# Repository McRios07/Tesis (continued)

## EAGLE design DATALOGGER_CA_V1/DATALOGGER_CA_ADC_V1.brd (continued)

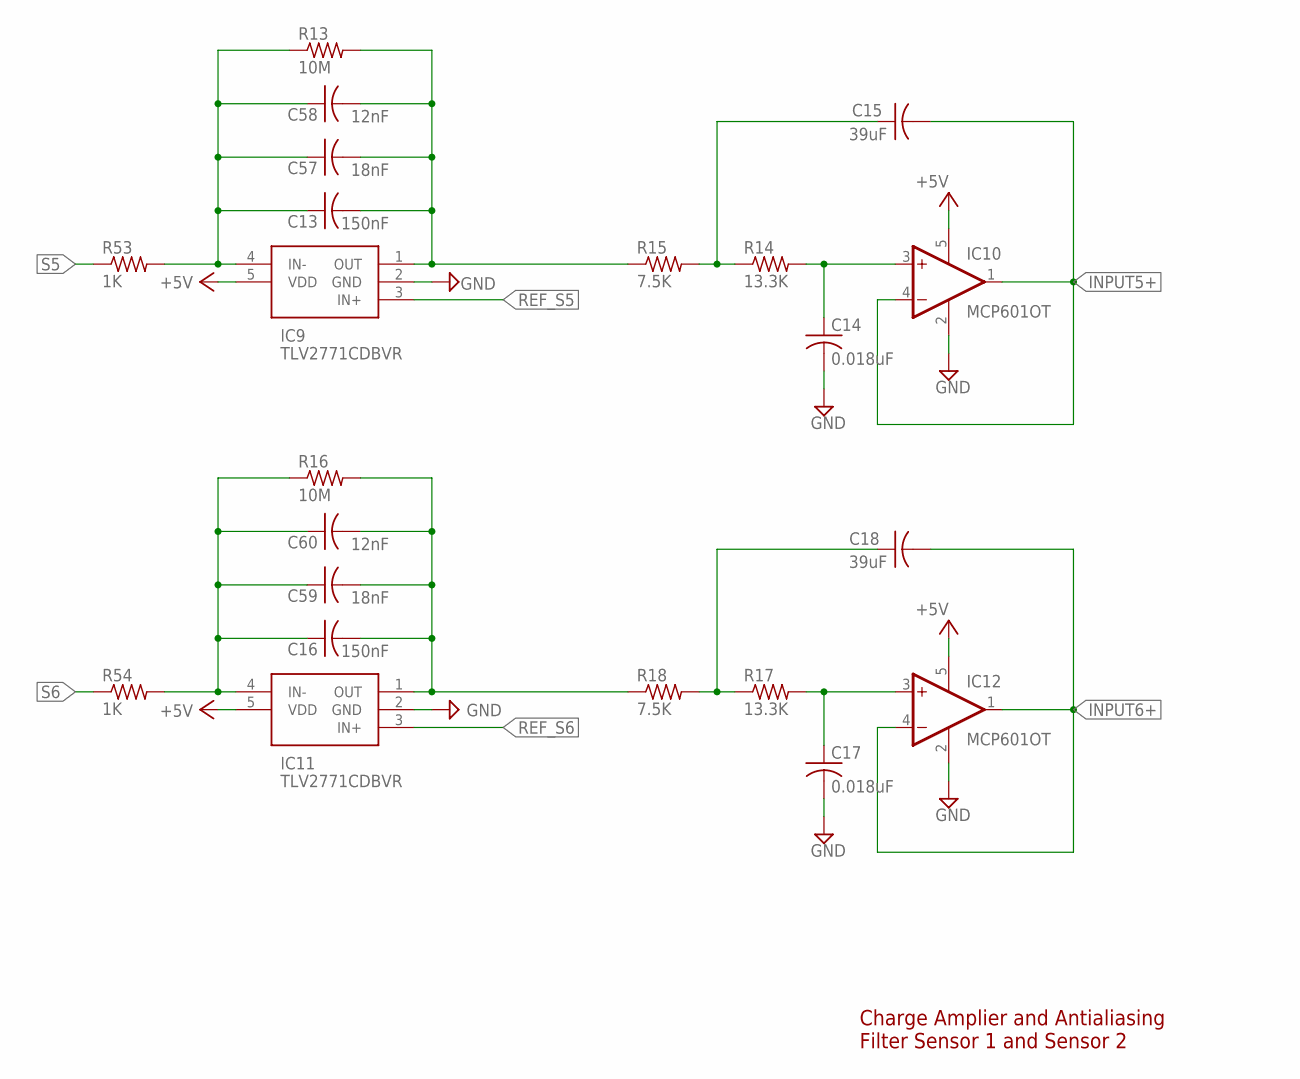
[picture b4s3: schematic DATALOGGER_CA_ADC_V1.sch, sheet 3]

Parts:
C13, C16: 150nF; C0805
C14, C17: 0.018uF; C0805
C15, C18: 39uF; C0805
C57, C59: 18nF; C0805
C58, C60: 12nF; C0805
IC9, IC11: TLV2771CDBVR; SOT95P280X145-5N
IC10, IC12: MCP601OT; SOT23-5
R13, R16: 10M; R0805
R14, R17: 13.3K; R0805
R15, R18: 7.5K; R0805
R53, R54: 1K; R0805

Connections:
+5V: IC9.5 (VDD), IC10.5 (V+), IC11.5 (VDD), IC12.5 (V+); also elsewhere on the board
GND: C14.2, C17.2, IC9.2 (GND), IC10.2 (V-), IC11.2 (GND), IC12.2 (V-); also elsewhere on the board
INPUT5+: C15.2, IC10.1 (OUT), IC10.4 (-IN); also elsewhere on the board
INPUT6+: C18.2, IC12.1 (OUT), IC12.4 (-IN); also elsewhere on the board
unnamed: C13.2, C57.2, C58.2, IC9.1 (OUT), R13.2, R15.1
unnamed: C14.1, IC10.3 (+IN), R14.2
unnamed: C15.1, R14.1, R15.2
unnamed: C16.2, C59.2, C60.2, IC11.1 (OUT), R16.2, R18.1
unnamed: C17.1, IC12.3 (+IN), R17.2
unnamed: C18.1, R17.1, R18.2
unnamed: C13.1, C57.1, C58.1, IC9.4 (IN-), R13.1, R53.2
unnamed: C16.1, C59.1, C60.1, IC11.4 (IN-), R16.1, R54.2
REF_S5: IC9.3 (IN+); also elsewhere on the board
REF_S6: IC11.3 (IN+); also elsewhere on the board
S5: R53.1; also elsewhere on the board
S6: R54.1; also elsewhere on the board

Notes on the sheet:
Charge Amplier and Antialiasing Filter Sensor 1 and Sensor 2

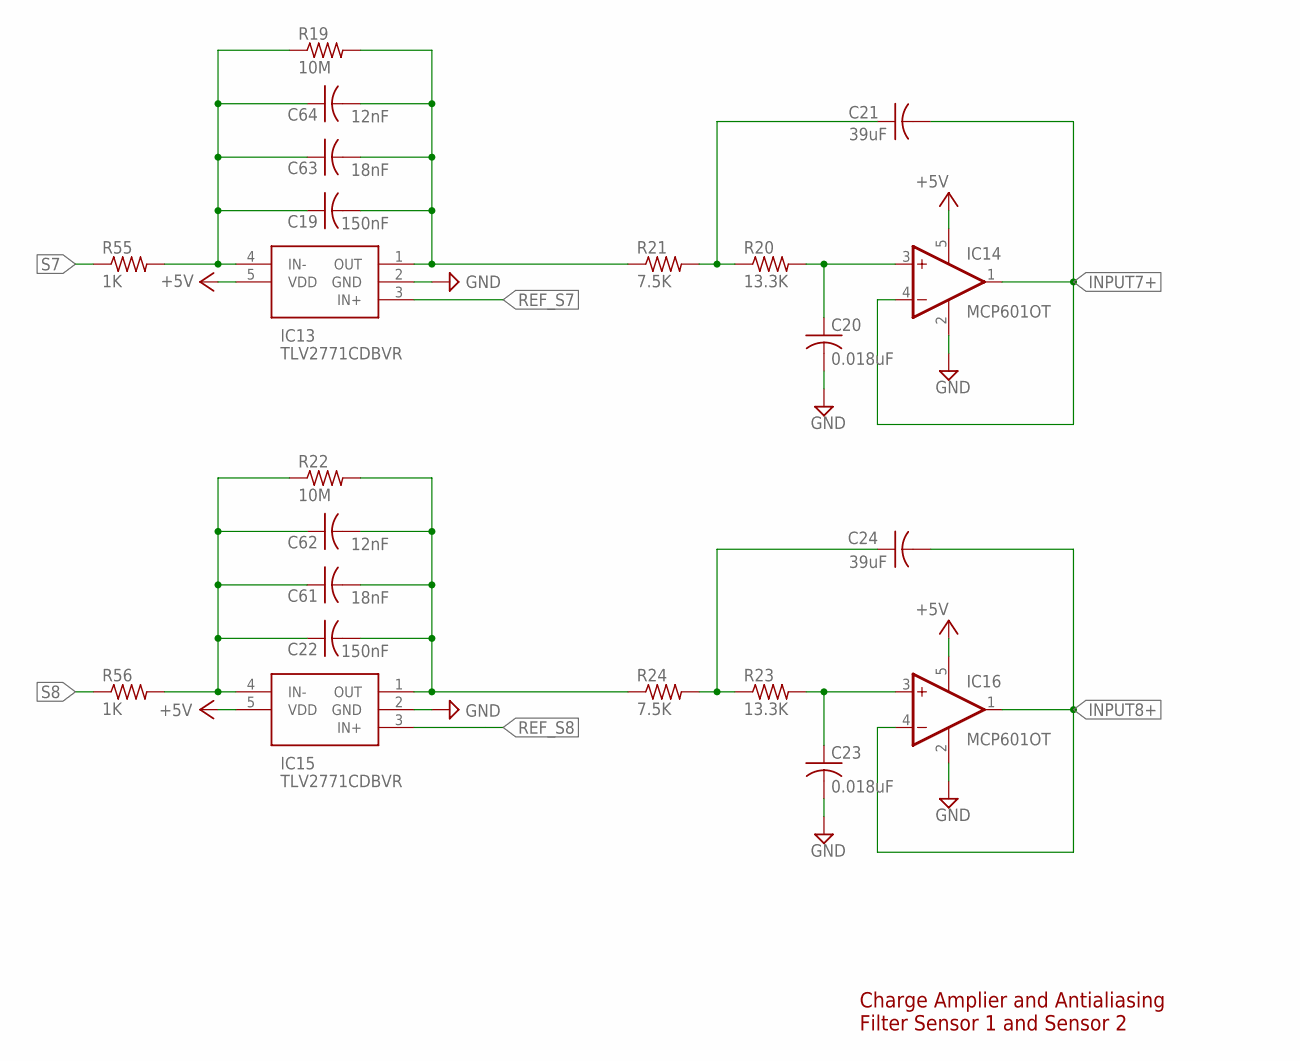
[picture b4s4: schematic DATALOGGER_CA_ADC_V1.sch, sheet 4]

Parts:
C19, C22: 150nF; C0805
C20, C23: 0.018uF; C0805
C21, C24: 39uF; C0805
C61, C63: 18nF; C0805
C62, C64: 12nF; C0805
IC13, IC15: TLV2771CDBVR; SOT95P280X145-5N
IC14, IC16: MCP601OT; SOT23-5
R19, R22: 10M; R0805
R20, R23: 13.3K; R0805
R21, R24: 7.5K; R0805
R55, R56: 1K; R0805

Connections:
+5V: IC13.5 (VDD), IC14.5 (V+), IC15.5 (VDD), IC16.5 (V+); also elsewhere on the board
GND: C20.2, C23.2, IC13.2 (GND), IC14.2 (V-), IC15.2 (GND), IC16.2 (V-); also elsewhere on the board
INPUT7+: C21.2, IC14.1 (OUT), IC14.4 (-IN); also elsewhere on the board
INPUT8+: C24.2, IC16.1 (OUT), IC16.4 (-IN); also elsewhere on the board
unnamed: C19.2, C63.2, C64.2, IC13.1 (OUT), R19.2, R21.1
unnamed: C20.1, IC14.3 (+IN), R20.2
unnamed: C21.1, R20.1, R21.2
unnamed: C22.2, C61.2, C62.2, IC15.1 (OUT), R22.2, R24.1
unnamed: C23.1, IC16.3 (+IN), R23.2
unnamed: C24.1, R23.1, R24.2
unnamed: C19.1, C63.1, C64.1, IC13.4 (IN-), R19.1, R55.2
unnamed: C22.1, C61.1, C62.1, IC15.4 (IN-), R22.1, R56.2
REF_S7: IC13.3 (IN+); also elsewhere on the board
REF_S8: IC15.3 (IN+); also elsewhere on the board
S7: R55.1; also elsewhere on the board
S8: R56.1; also elsewhere on the board

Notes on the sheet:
Charge Amplier and Antialiasing Filter Sensor 1 and Sensor 2

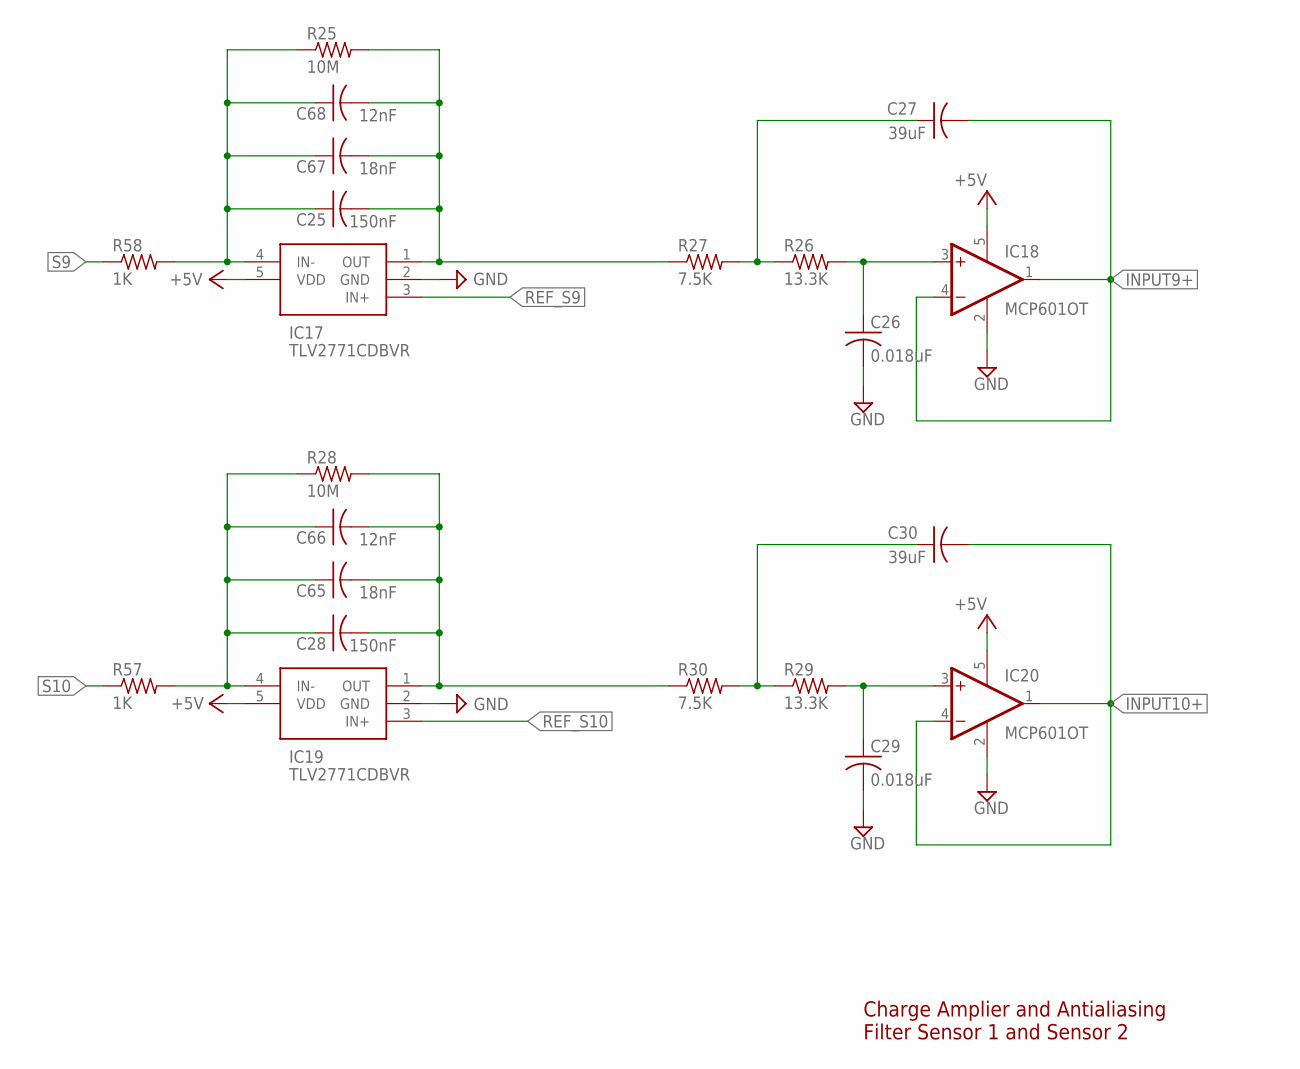
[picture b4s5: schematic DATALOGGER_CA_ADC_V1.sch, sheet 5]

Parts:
C25, C28: 150nF; C0805
C26, C29: 0.018uF; C0805
C27, C30: 39uF; C0805
C65, C67: 18nF; C0805
C66, C68: 12nF; C0805
IC17, IC19: TLV2771CDBVR; SOT95P280X145-5N
IC18, IC20: MCP601OT; SOT23-5
R25, R28: 10M; R0805
R26, R29: 13.3K; R0805
R27, R30: 7.5K; R0805
R57, R58: 1K; R0805

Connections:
+5V: IC17.5 (VDD), IC18.5 (V+), IC19.5 (VDD), IC20.5 (V+); also elsewhere on the board
GND: C26.2, C29.2, IC17.2 (GND), IC18.2 (V-), IC19.2 (GND), IC20.2 (V-); also elsewhere on the board
INPUT9+: C27.2, IC18.1 (OUT), IC18.4 (-IN); also elsewhere on the board
INPUT10+: C30.2, IC20.1 (OUT), IC20.4 (-IN); also elsewhere on the board
unnamed: C25.2, C67.2, C68.2, IC17.1 (OUT), R25.2, R27.1
unnamed: C26.1, IC18.3 (+IN), R26.2
unnamed: C27.1, R26.1, R27.2
unnamed: C28.2, C65.2, C66.2, IC19.1 (OUT), R28.2, R30.1
unnamed: C29.1, IC20.3 (+IN), R29.2
unnamed: C30.1, R29.1, R30.2
unnamed: C25.1, C67.1, C68.1, IC17.4 (IN-), R25.1, R58.2
unnamed: C28.1, C65.1, C66.1, IC19.4 (IN-), R28.1, R57.2
REF_S9: IC17.3 (IN+); also elsewhere on the board
REF_S10: IC19.3 (IN+); also elsewhere on the board
S9: R58.1; also elsewhere on the board
S10: R57.1; also elsewhere on the board

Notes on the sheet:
Charge Amplier and Antialiasing Filter Sensor 1 and Sensor 2

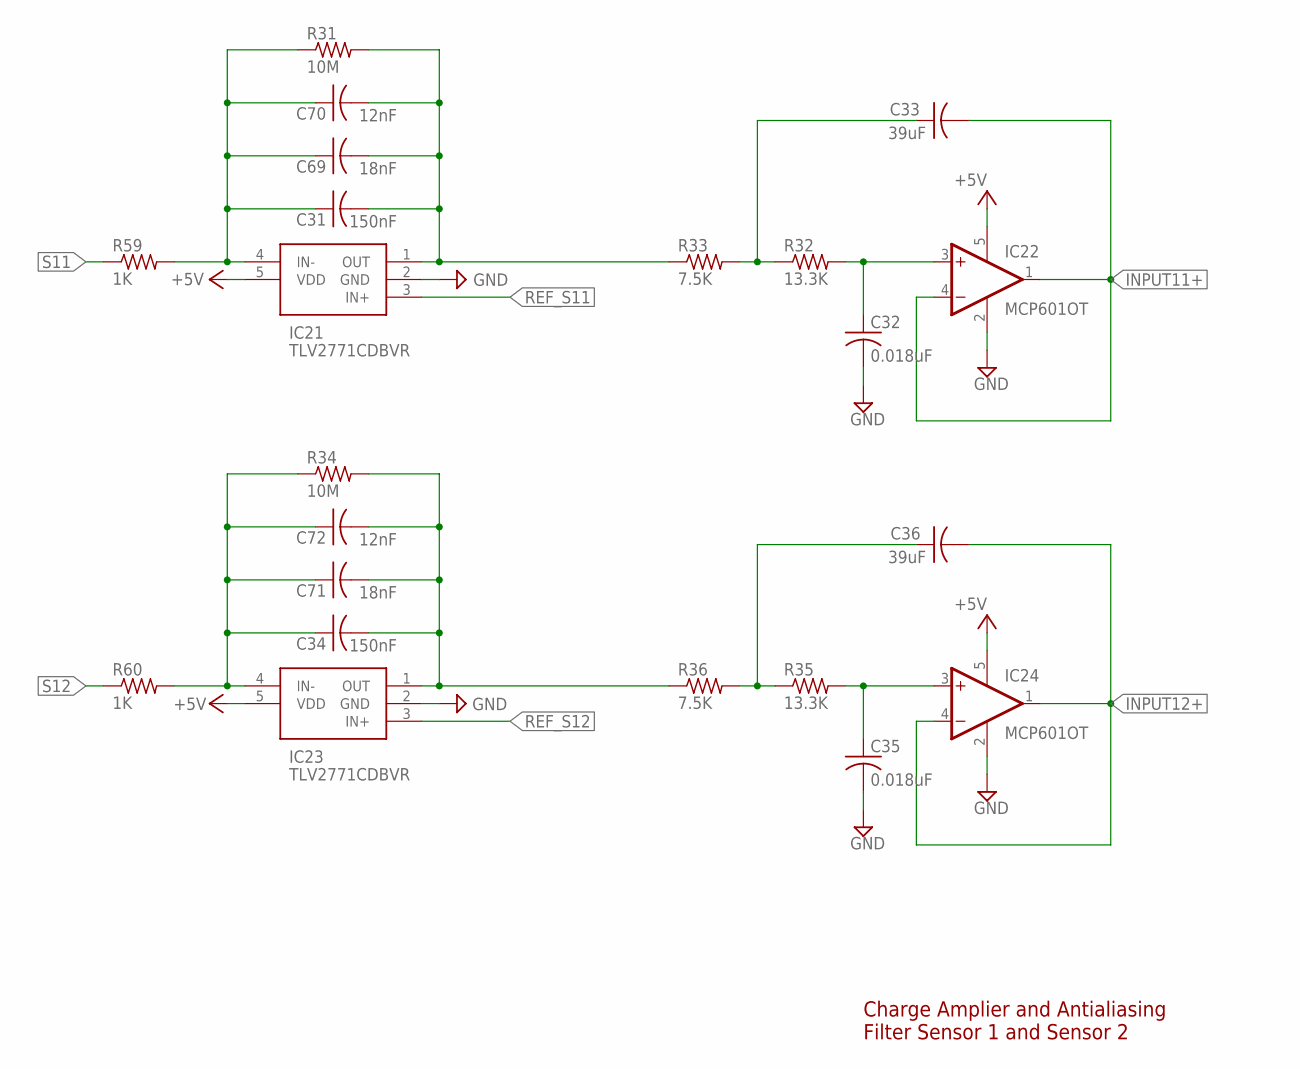
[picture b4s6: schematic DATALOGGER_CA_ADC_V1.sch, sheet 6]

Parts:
C31, C34: 150nF; C0805
C32, C35: 0.018uF; C0805
C33, C36: 39uF; C0805
C69, C71: 18nF; C0805
C70, C72: 12nF; C0805
IC21, IC23: TLV2771CDBVR; SOT95P280X145-5N
IC22, IC24: MCP601OT; SOT23-5
R31, R34: 10M; R0805
R32, R35: 13.3K; R0805
R33, R36: 7.5K; R0805
R59, R60: 1K; R0805

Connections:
+5V: IC21.5 (VDD), IC22.5 (V+), IC23.5 (VDD), IC24.5 (V+); also elsewhere on the board
GND: C32.2, C35.2, IC21.2 (GND), IC22.2 (V-), IC23.2 (GND), IC24.2 (V-); also elsewhere on the board
INPUT11+: C33.2, IC22.1 (OUT), IC22.4 (-IN); also elsewhere on the board
INPUT12+: C36.2, IC24.1 (OUT), IC24.4 (-IN); also elsewhere on the board
unnamed: C31.2, C69.2, C70.2, IC21.1 (OUT), R31.2, R33.1
unnamed: C32.1, IC22.3 (+IN), R32.2
unnamed: C33.1, R32.1, R33.2
unnamed: C34.2, C71.2, C72.2, IC23.1 (OUT), R34.2, R36.1
unnamed: C35.1, IC24.3 (+IN), R35.2
unnamed: C36.1, R35.1, R36.2
unnamed: C31.1, C69.1, C70.1, IC21.4 (IN-), R31.1, R59.2
unnamed: C34.1, C71.1, C72.1, IC23.4 (IN-), R34.1, R60.2
REF_S11: IC21.3 (IN+); also elsewhere on the board
REF_S12: IC23.3 (IN+); also elsewhere on the board
S11: R59.1; also elsewhere on the board
S12: R60.1; also elsewhere on the board

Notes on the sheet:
Charge Amplier and Antialiasing Filter Sensor 1 and Sensor 2

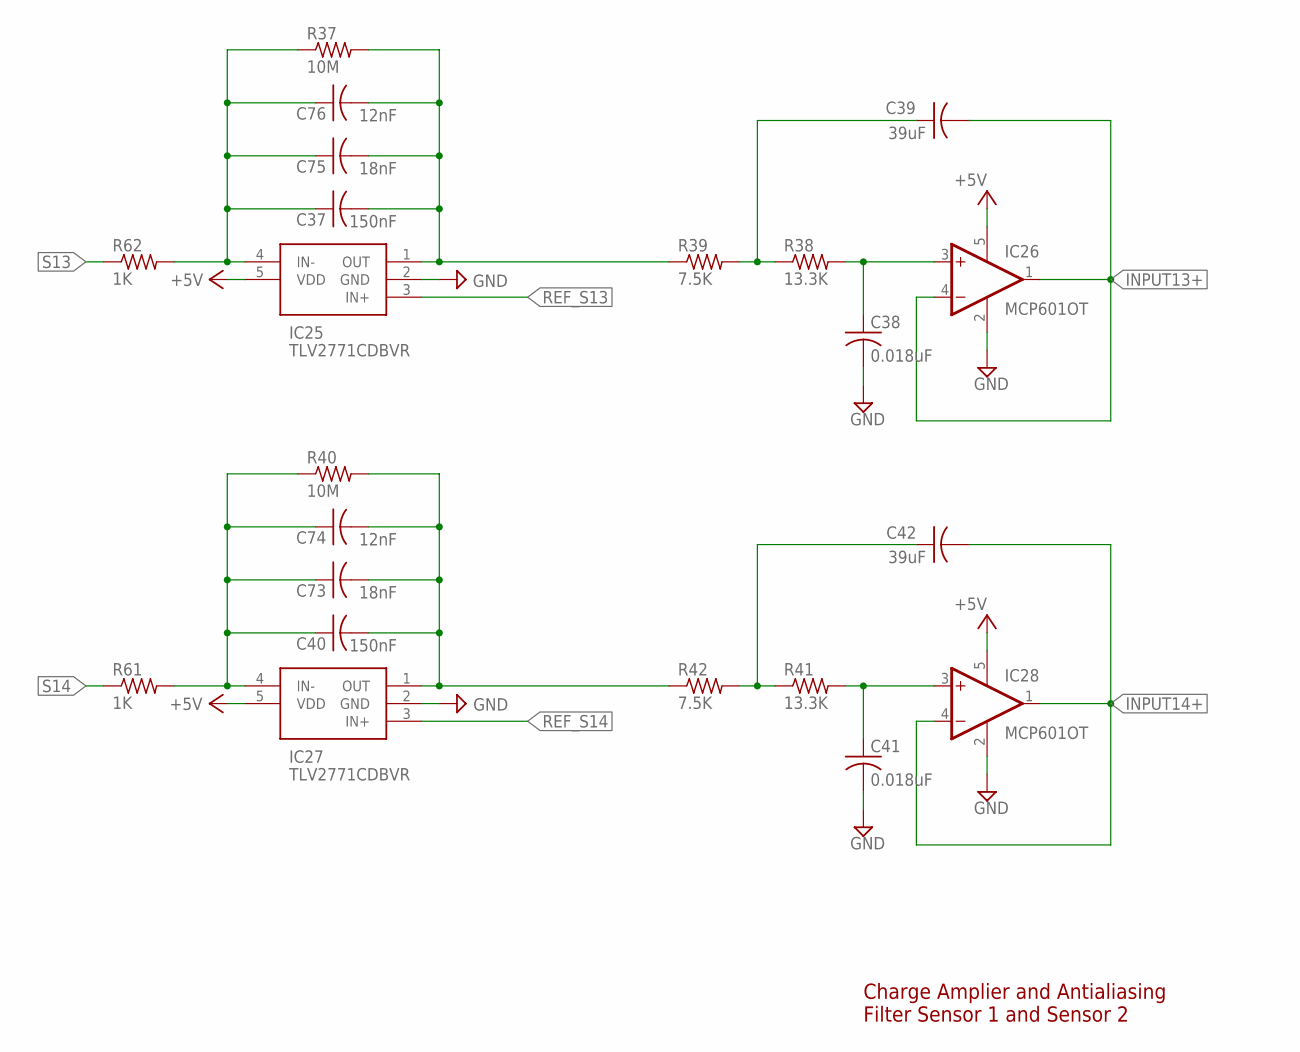
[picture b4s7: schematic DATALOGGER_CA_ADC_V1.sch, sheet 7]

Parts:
C37, C40: 150nF; C0805
C38, C41: 0.018uF; C0805
C39, C42: 39uF; C0805
C73, C75: 18nF; C0805
C74, C76: 12nF; C0805
IC25, IC27: TLV2771CDBVR; SOT95P280X145-5N
IC26, IC28: MCP601OT; SOT23-5
R37, R40: 10M; R0805
R38, R41: 13.3K; R0805
R39, R42: 7.5K; R0805
R61, R62: 1K; R0805

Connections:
+5V: IC25.5 (VDD), IC26.5 (V+), IC27.5 (VDD), IC28.5 (V+); also elsewhere on the board
GND: C38.2, C41.2, IC25.2 (GND), IC26.2 (V-), IC27.2 (GND), IC28.2 (V-); also elsewhere on the board
INPUT13+: C39.2, IC26.1 (OUT), IC26.4 (-IN); also elsewhere on the board
INPUT14+: C42.2, IC28.1 (OUT), IC28.4 (-IN); also elsewhere on the board
unnamed: C37.2, C75.2, C76.2, IC25.1 (OUT), R37.2, R39.1
unnamed: C38.1, IC26.3 (+IN), R38.2
unnamed: C39.1, R38.1, R39.2
unnamed: C40.2, C73.2, C74.2, IC27.1 (OUT), R40.2, R42.1
unnamed: C41.1, IC28.3 (+IN), R41.2
unnamed: C42.1, R41.1, R42.2
unnamed: C37.1, C75.1, C76.1, IC25.4 (IN-), R37.1, R62.2
unnamed: C40.1, C73.1, C74.1, IC27.4 (IN-), R40.1, R61.2
REF_S13: IC25.3 (IN+); also elsewhere on the board
REF_S14: IC27.3 (IN+); also elsewhere on the board
S13: R62.1; also elsewhere on the board
S14: R61.1; also elsewhere on the board

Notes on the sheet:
Charge Amplier and Antialiasing Filter Sensor 1 and Sensor 2

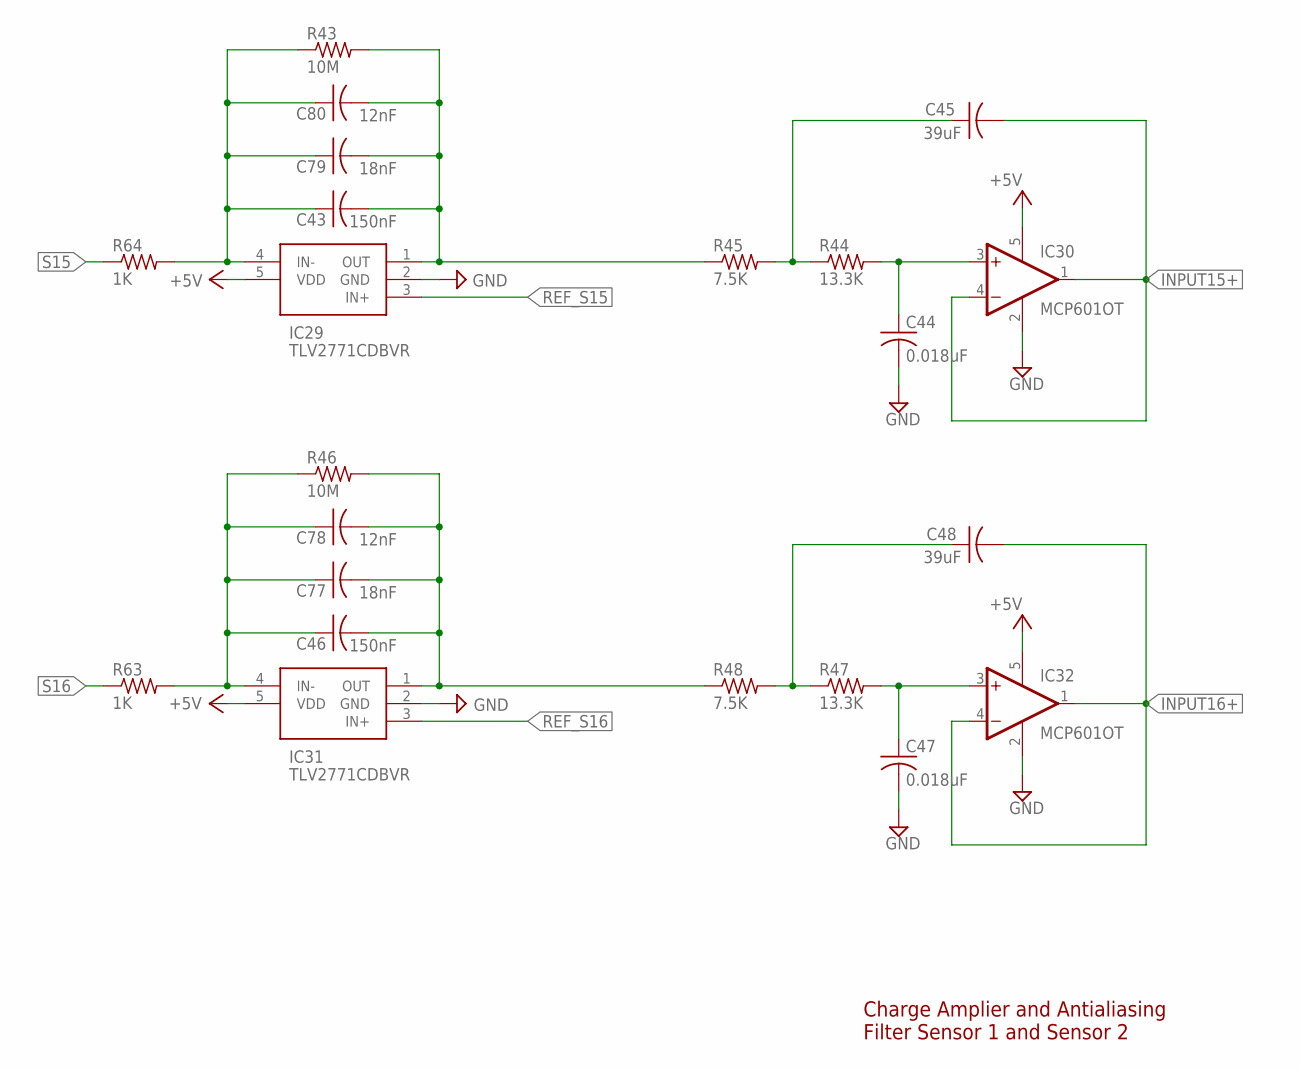
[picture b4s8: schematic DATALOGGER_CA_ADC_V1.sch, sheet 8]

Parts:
C43, C46: 150nF; C0805
C44, C47: 0.018uF; C0805
C45, C48: 39uF; C0805
C77, C79: 18nF; C0805
C78, C80: 12nF; C0805
IC29, IC31: TLV2771CDBVR; SOT95P280X145-5N
IC30, IC32: MCP601OT; SOT23-5
R43, R46: 10M; R0805
R44, R47: 13.3K; R0805
R45, R48: 7.5K; R0805
R63, R64: 1K; R0805

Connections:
+5V: IC29.5 (VDD), IC30.5 (V+), IC31.5 (VDD), IC32.5 (V+); also elsewhere on the board
GND: C44.2, C47.2, IC29.2 (GND), IC30.2 (V-), IC31.2 (GND), IC32.2 (V-); also elsewhere on the board
INPUT15+: C45.2, IC30.1 (OUT), IC30.4 (-IN); also elsewhere on the board
INPUT16+: C48.2, IC32.1 (OUT), IC32.4 (-IN); also elsewhere on the board
unnamed: C43.2, C79.2, C80.2, IC29.1 (OUT), R43.2, R45.1
unnamed: C44.1, IC30.3 (+IN), R44.2
unnamed: C45.1, R44.1, R45.2
unnamed: C46.2, C77.2, C78.2, IC31.1 (OUT), R46.2, R48.1
unnamed: C47.1, IC32.3 (+IN), R47.2
unnamed: C48.1, R47.1, R48.2
unnamed: C43.1, C79.1, C80.1, IC29.4 (IN-), R43.1, R64.2
unnamed: C46.1, C77.1, C78.1, IC31.4 (IN-), R46.1, R63.2
REF_S15: IC29.3 (IN+); also elsewhere on the board
REF_S16: IC31.3 (IN+); also elsewhere on the board
S15: R64.1; also elsewhere on the board
S16: R63.1; also elsewhere on the board

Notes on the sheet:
Charge Amplier and Antialiasing Filter Sensor 1 and Sensor 2

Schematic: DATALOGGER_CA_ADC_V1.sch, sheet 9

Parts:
J1, J2, J3, J4: 1985027
JP1: PINHD-2X20; 2X20

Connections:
+5V: JP1.39, JP1.40; also elsewhere on the board
+12V: JP1.35, JP1.36
GND: JP1.2, JP1.4, JP1.6, JP1.8, JP1.10, JP1.12, JP1.14, JP1.16, JP1.18, JP1.20, JP1.22, JP1.24, JP1.26, JP1.28, JP1.30, JP1.32, JP1.33, JP1.34, JP1.37, JP1.38; also elsewhere on the board
INPUT1+: JP1.1; also elsewhere on the board
INPUT2+: JP1.3; also elsewhere on the board
INPUT3+: JP1.5; also elsewhere on the board
INPUT4+: JP1.7; also elsewhere on the board
INPUT5+: JP1.9; also elsewhere on the board
INPUT6+: JP1.11; also elsewhere on the board
INPUT7+: JP1.13; also elsewhere on the board
INPUT8+: JP1.15; also elsewhere on the board
INPUT9+: JP1.17; also elsewhere on the board
INPUT10+: JP1.19; also elsewhere on the board
INPUT11+: JP1.21; also elsewhere on the board
INPUT12+: JP1.23; also elsewhere on the board
INPUT13+: JP1.25; also elsewhere on the board
INPUT14+: JP1.27; also elsewhere on the board
INPUT15+: JP1.29; also elsewhere on the board
INPUT16+: JP1.31; also elsewhere on the board
REF_S1: J1.2; also elsewhere on the board
REF_S2: J1.4; also elsewhere on the board
REF_S3: J1.6; also elsewhere on the board
REF_S4: J1.8; also elsewhere on the board
REF_S5: J2.2; also elsewhere on the board
REF_S6: J2.4; also elsewhere on the board
REF_S7: J2.6; also elsewhere on the board
REF_S8: J2.8; also elsewhere on the board
REF_S9: J3.2; also elsewhere on the board
REF_S10: J3.4; also elsewhere on the board
REF_S11: J3.6; also elsewhere on the board
REF_S12: J3.8; also elsewhere on the board
REF_S13: J4.2; also elsewhere on the board
REF_S14: J4.4; also elsewhere on the board
REF_S15: J4.6; also elsewhere on the board
REF_S16: J4.8; also elsewhere on the board
S1: J1.1; also elsewhere on the board
S2: J1.3; also elsewhere on the board
S3: J1.5; also elsewhere on the board
S4: J1.7; also elsewhere on the board
S5: J2.1; also elsewhere on the board
S6: J2.3; also elsewhere on the board
S7: J2.5; also elsewhere on the board
S8: J2.7; also elsewhere on the board
S9: J3.1; also elsewhere on the board
S10: J3.3; also elsewhere on the board
S11: J3.5; also elsewhere on the board
S12: J3.7; also elsewhere on the board
S13: J4.1; also elsewhere on the board
S14: J4.3; also elsewhere on the board
S15: J4.5; also elsewhere on the board
S16: J4.7; also elsewhere on the board

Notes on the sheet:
Charge Amplier and Antialiasing Filter Sensor 1 and Sensor 2

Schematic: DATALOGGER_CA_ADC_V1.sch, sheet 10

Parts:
C81, C82, C83, C84, C85, C86, C87, C88, C89, C90, C91, C92, C93, C94, C95, C96: 1uF; C0805
U1, U2, U3, U4, U5, U6, U7, U8: REF5025AID; D8

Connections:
+5V: C81.1, C83.1, C85.1, C87.1, C89.1, C91.1, C93.1, C95.1, U1.2 (VIN), U2.2 (VIN), U3.2 (VIN), U4.2 (VIN), U5.2 (VIN), U6.2 (VIN), U7.2 (VIN), U8.2 (VIN); also elsewhere on the board
GND: C81.2, C82.2, C83.2, C84.2, C85.2, C86.2, C87.2, C88.2, C89.2, C90.2, C91.2, C92.2, C93.2, C94.2, C95.2, C96.2, U1.4 (GND), U2.4 (GND), U3.4 (GND), U4.4 (GND), U5.4 (GND), U6.4 (GND), U7.4 (GND), U8.4 (GND); also elsewhere on the board
REF_S1: C82.1, U1.6 (VOUT); also elsewhere on the board
REF_S2: C84.1, U2.6 (VOUT); also elsewhere on the board
REF_S3: C86.1, U3.6 (VOUT); also elsewhere on the board
REF_S4: C88.1, U4.6 (VOUT); also elsewhere on the board
REF_S5: C90.1, U5.6 (VOUT); also elsewhere on the board
REF_S6: C92.1, U6.6 (VOUT); also elsewhere on the board
REF_S7: C94.1, U7.6 (VOUT); also elsewhere on the board
REF_S8: C96.1, U8.6 (VOUT); also elsewhere on the board

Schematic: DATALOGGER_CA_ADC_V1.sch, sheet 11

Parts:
C97, C98, C99, C100, C101, C102, C103, C104, C105, C106, C107, C108, C109, C110, C111, C112: 1uF; C0805
U9, U10, U11, U12, U13, U14, U15, U16: REF5025AID; D8

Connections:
+5V: C97.1, C99.1, C101.1, C103.1, C105.1, C107.1, C109.1, C111.1, U9.2 (VIN), U10.2 (VIN), U11.2 (VIN), U12.2 (VIN), U13.2 (VIN), U14.2 (VIN), U15.2 (VIN), U16.2 (VIN); also elsewhere on the board
GND: C97.2, C98.2, C99.2, C100.2, C101.2, C102.2, C103.2, C104.2, C105.2, C106.2, C107.2, C108.2, C109.2, C110.2, C111.2, C112.2, U9.4 (GND), U10.4 (GND), U11.4 (GND), U12.4 (GND), U13.4 (GND), U14.4 (GND), U15.4 (GND), U16.4 (GND); also elsewhere on the board
REF_S9: C98.1, U9.6 (VOUT); also elsewhere on the board
REF_S10: C100.1, U10.6 (VOUT); also elsewhere on the board
REF_S11: C102.1, U11.6 (VOUT); also elsewhere on the board
REF_S12: C104.1, U12.6 (VOUT); also elsewhere on the board
REF_S13: C106.1, U13.6 (VOUT); also elsewhere on the board
REF_S14: C108.1, U14.6 (VOUT); also elsewhere on the board
REF_S15: C110.1, U15.6 (VOUT); also elsewhere on the board
REF_S16: C112.1, U16.6 (VOUT); also elsewhere on the board

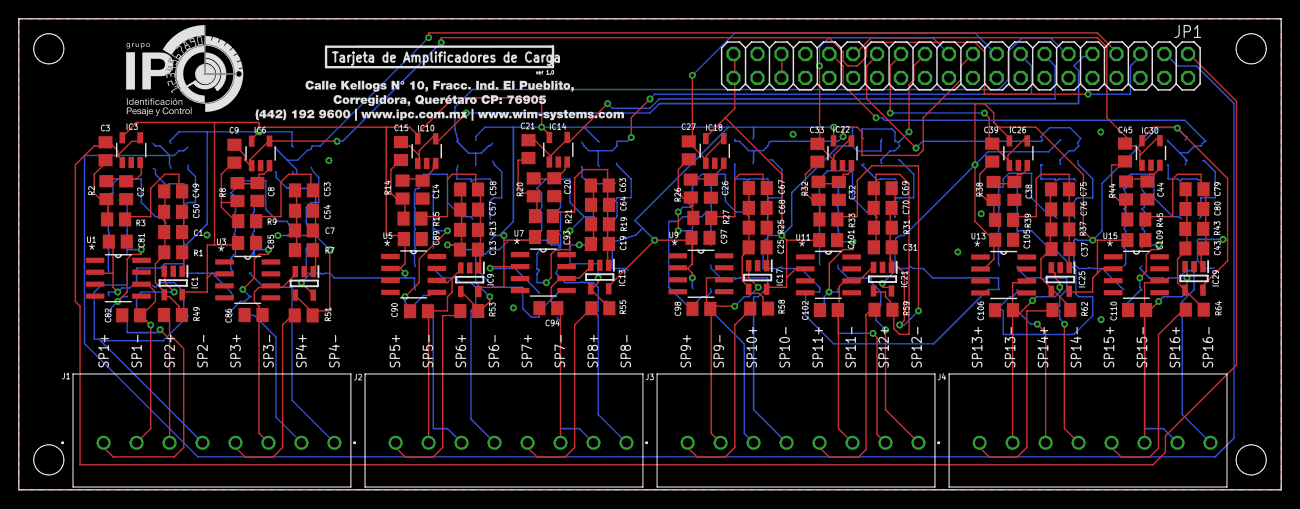
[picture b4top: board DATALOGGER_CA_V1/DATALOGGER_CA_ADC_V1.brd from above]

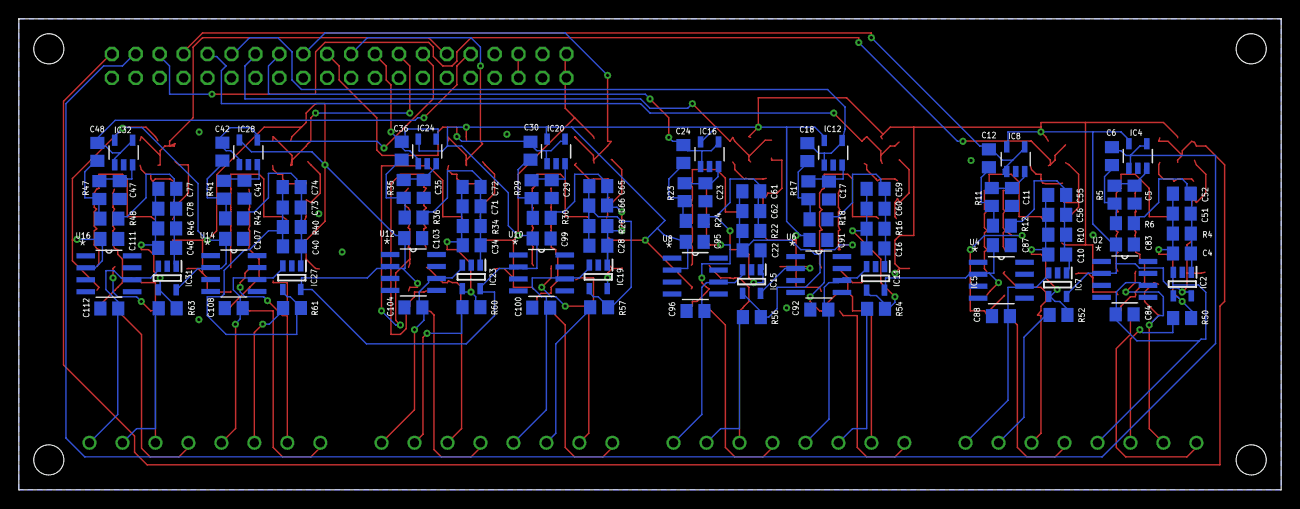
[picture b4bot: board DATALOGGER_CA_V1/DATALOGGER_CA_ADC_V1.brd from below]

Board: 2 copper layers, 134.0 x 50.0 mm, 229 parts (112 on the bottom side), 115 nets.

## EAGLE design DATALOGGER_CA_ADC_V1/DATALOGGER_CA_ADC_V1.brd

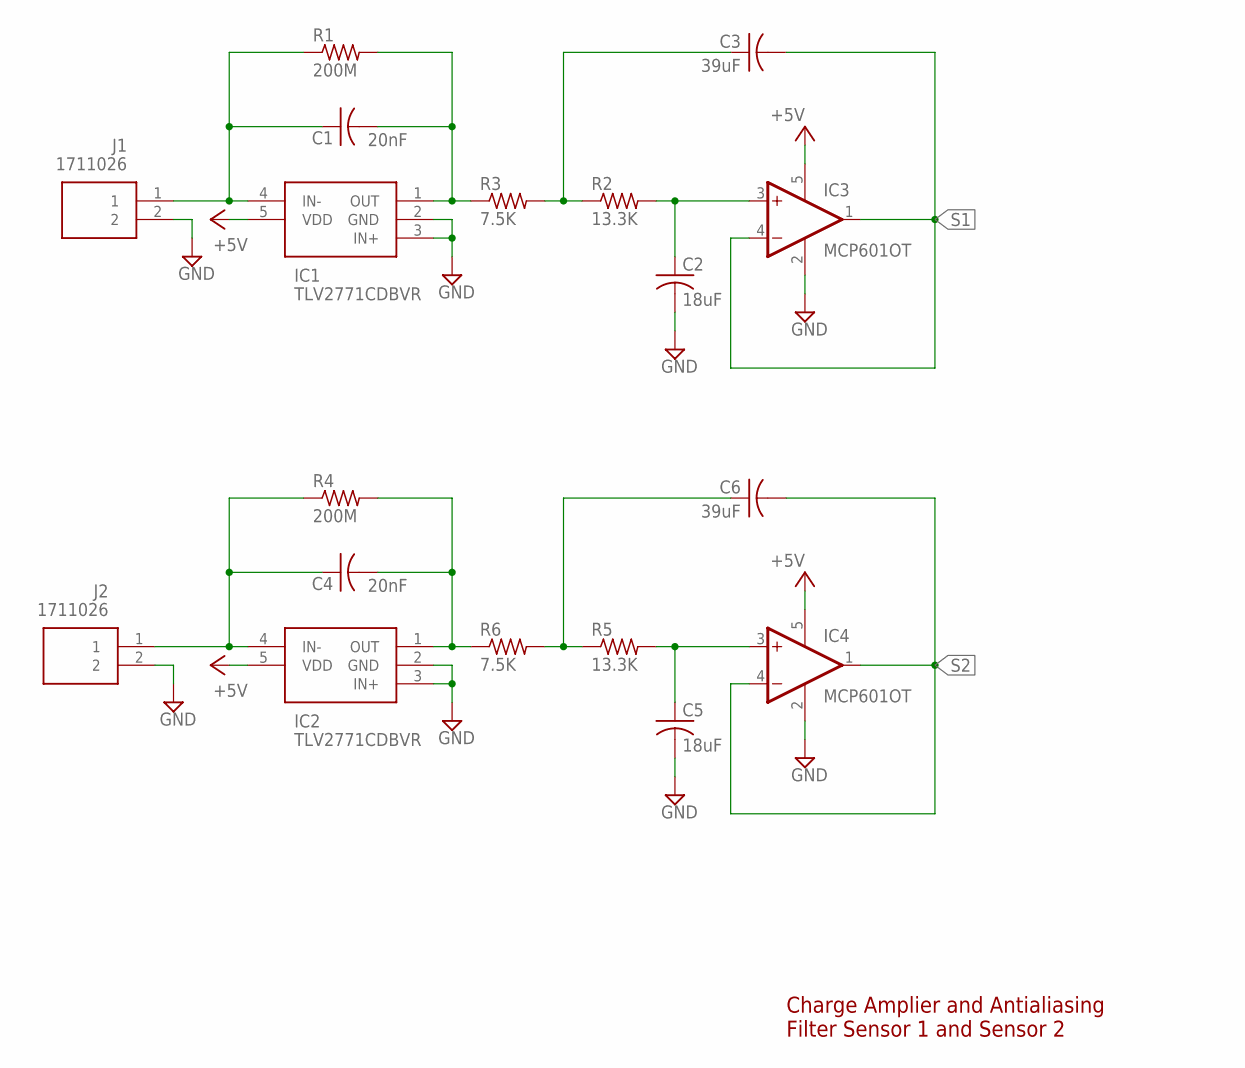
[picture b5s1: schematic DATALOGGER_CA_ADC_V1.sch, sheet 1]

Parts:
C1, C4: 20nF; C0805
C2, C5: 18uF; C0805
C3, C6: 39uF; C0805
IC1, IC2: TLV2771CDBVR; SOT95P280X145-5N
IC3, IC4: MCP601OT; SOT23-5
J1, J2: 1711026; SHDR2W110P0X500_1X2_1000X1120X
R1, R4: 200M; R0805
R2, R5: 13.3K; R0805
R3, R6: 7.5K; R0805

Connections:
+5V: IC1.5 (VDD), IC2.5 (VDD), IC3.5 (V+), IC4.5 (V+); also elsewhere on the board
GND: C2.2, C5.2, IC1.2 (GND), IC1.3 (IN+), IC2.2 (GND), IC2.3 (IN+), IC3.2 (V-), IC4.2 (V-), J1.2, J2.2; also elsewhere on the board
unnamed: C1.1, IC1.4 (IN-), J1.1, R1.1
unnamed: C1.2, IC1.1 (OUT), R1.2, R3.1
unnamed: C2.1, IC3.3 (+IN), R2.2
unnamed: C3.1, R2.1, R3.2
unnamed: C4.1, IC2.4 (IN-), J2.1, R4.1
unnamed: C4.2, IC2.1 (OUT), R4.2, R6.1
unnamed: C5.1, IC4.3 (+IN), R5.2
unnamed: C6.1, R5.1, R6.2
S1: C3.2, IC3.1 (OUT), IC3.4 (-IN); also elsewhere on the board
S2: C6.2, IC4.1 (OUT), IC4.4 (-IN); also elsewhere on the board

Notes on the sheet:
Charge Amplier and Antialiasing Filter Sensor 1 and Sensor 2

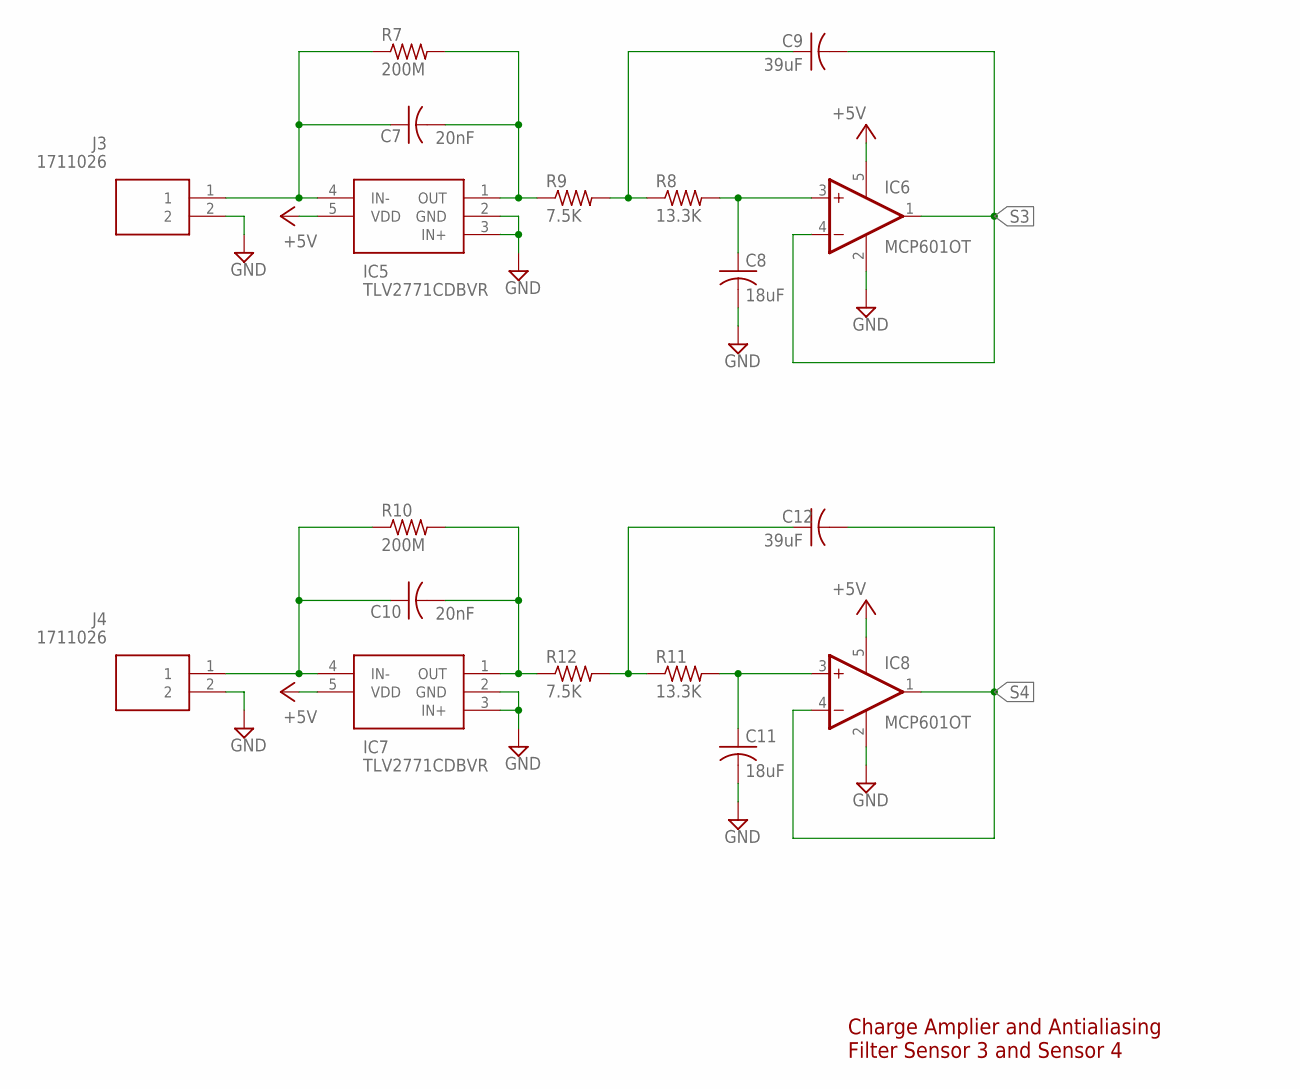
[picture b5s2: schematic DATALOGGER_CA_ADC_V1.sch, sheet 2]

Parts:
C7, C10: 20nF; C0805
C8, C11: 18uF; C0805
C9, C12: 39uF; C0805
IC5, IC7: TLV2771CDBVR; SOT95P280X145-5N
IC6, IC8: MCP601OT; SOT23-5
J3, J4: 1711026; SHDR2W110P0X500_1X2_1000X1120X
R7, R10: 200M; R0805
R8, R11: 13.3K; R0805
R9, R12: 7.5K; R0805

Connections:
+5V: IC5.5 (VDD), IC6.5 (V+), IC7.5 (VDD), IC8.5 (V+); also elsewhere on the board
GND: C8.2, C11.2, IC5.2 (GND), IC5.3 (IN+), IC6.2 (V-), IC7.2 (GND), IC7.3 (IN+), IC8.2 (V-), J3.2, J4.2; also elsewhere on the board
unnamed: C7.1, IC5.4 (IN-), J3.1, R7.1
unnamed: C7.2, IC5.1 (OUT), R7.2, R9.1
unnamed: C8.1, IC6.3 (+IN), R8.2
unnamed: C9.1, R8.1, R9.2
unnamed: C10.1, IC7.4 (IN-), J4.1, R10.1
unnamed: C10.2, IC7.1 (OUT), R10.2, R12.1
unnamed: C11.1, IC8.3 (+IN), R11.2
unnamed: C12.1, R11.1, R12.2
S3: C9.2, IC6.1 (OUT), IC6.4 (-IN); also elsewhere on the board
S4: C12.2, IC8.1 (OUT), IC8.4 (-IN); also elsewhere on the board

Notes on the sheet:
Charge Amplier and Antialiasing Filter Sensor 3 and Sensor 4
